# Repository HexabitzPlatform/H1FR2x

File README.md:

# H1FR2x-Hardware
Hexabitz SX1276 LoRa Module 915 MHz Module Hardware Design

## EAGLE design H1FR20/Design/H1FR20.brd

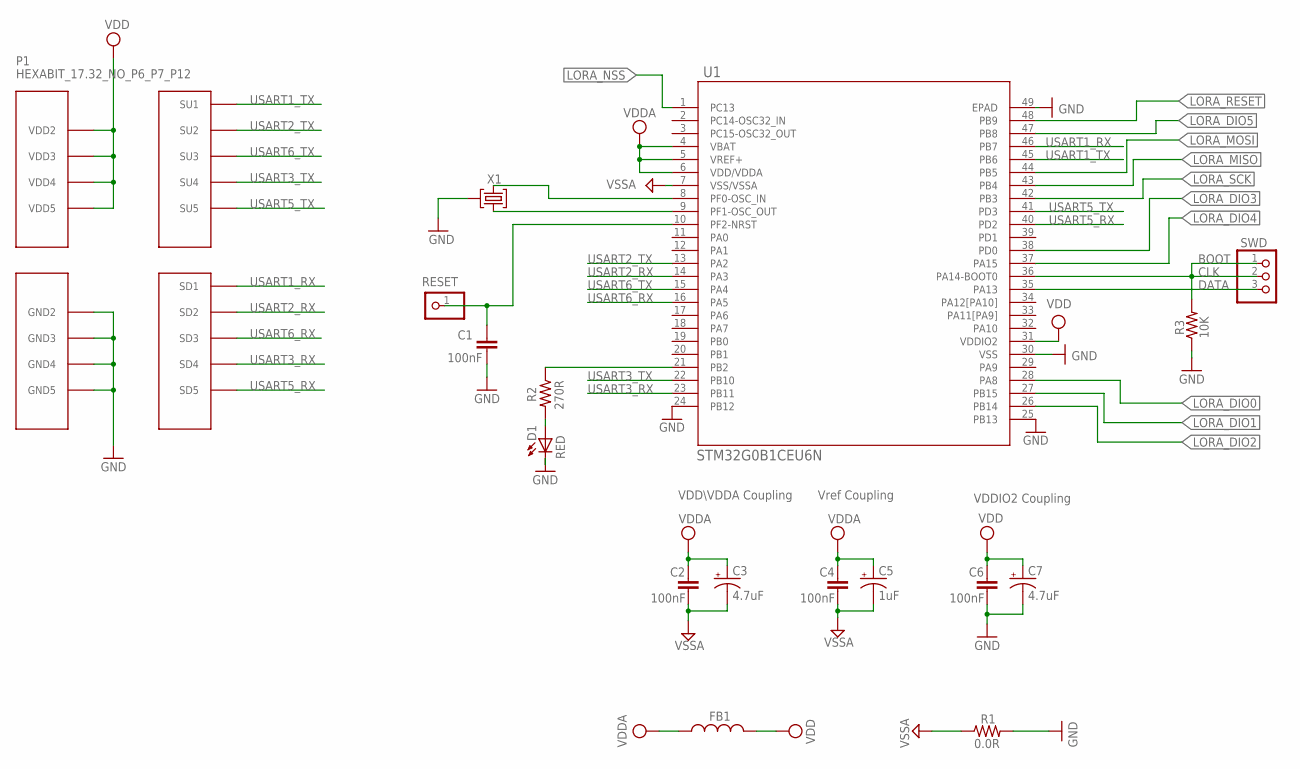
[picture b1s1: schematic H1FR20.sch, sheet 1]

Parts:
C1, C2, C4, C6: 100nF; C-0603
C3, C7: 4.7uF; C-0805-POL
C5: 1uF; C-0805-POL
D1: RED; VLMS1300-GS08; MPN VLMS1300-GS08
FB1: FB-0603
P1: HEXABIT_17.32_NO_P6_P7_P12
R1: 0.0R; R-0603
R2: 270R; R-0603
R3: 10K; R-0603
RESET: R; 1X01
SWD: PINHD-1X3SWD; SWD
U1: STM32G0B1CEU6N; HEXABITZ_ICS_QFN_B1CEU6_STM-L
X1: XTALL_CSTCE8M00G52

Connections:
CLK: R3.2, SWD.1, SWD.2, U1.36 (PA14-BOOT0)
DATA: SWD.3, U1.35 (PA13)
GND: C1.2, C6.2, C7.2 (-), D1.C, P1.PAD_PD8 (GND2), P1.PAD_PD9 (GND3), P1.PAD_PD10 (GND4), P1.PAD_PD11 (GND5), R1.2, R3.1, U1.24 (PB12), U1.25 (PB13), U1.30 (VSS), U1.49 (EPAD), X1.P$2 (2); also elsewhere on the board
LORA_DIO0: U1.28 (PA8); also elsewhere on the board
LORA_DIO1: U1.27 (PB15); also elsewhere on the board
LORA_DIO2: U1.26 (PB14); also elsewhere on the board
LORA_DIO3: U1.38 (PD0); also elsewhere on the board
LORA_DIO4: U1.37 (PA15); also elsewhere on the board
LORA_DIO5: U1.47 (PB8); also elsewhere on the board
LORA_MISO: U1.43 (PB4); also elsewhere on the board
LORA_MOSI: U1.44 (PB5); also elsewhere on the board
LORA_NSS: U1.1 (PC13); also elsewhere on the board
LORA_RESET: U1.48 (PB9); also elsewhere on the board
LORA_SCK: U1.42 (PB3); also elsewhere on the board
unnamed: D1.A, R2.2
unnamed: R2.1, U1.21 (PB2)
unnamed: U1.9 (PF1-OSC_OUT), X1.P$1 (1)
unnamed: U1.8 (PF0-OSC_IN), X1.P$3 (3)
unnamed: C1.1, RESET.1, U1.10 (PF2-NRST)
USART1_RX: P1.PAD_PD1 (SD1), U1.46 (PB7)
USART1_TX: P1.PAD_PU1 (SU1), U1.45 (PB6)
USART2_RX: P1.PAD_PD2 (SD2), U1.14 (PA3)
USART2_TX: P1.PAD_PU2 (SU2), U1.13 (PA2)
USART3_RX: P1.PAD_PD4 (SD4), U1.23 (PB11)
USART3_TX: P1.PAD_PU4 (SU4), U1.22 (PB10)
USART5_RX: P1.PAD_PD5 (SD5), U1.40 (PD2)
USART5_TX: P1.PAD_PU5 (SU5), U1.41 (PD3)
USART6_RX: P1.PAD_PD3 (SD3), U1.16 (PA5)
USART6_TX: P1.PAD_PU3 (SU3), U1.15 (PA4)
VDD: C6.1, C7.1 (+), FB1.2, P1.PAD_PU8 (VDD2), P1.PAD_PU9 (VDD3), P1.PAD_PU10 (VDD4), P1.PAD_PU11 (VDD5), U1.31 (VDDIO2); also elsewhere on the board
VDDA: C2.1, C3.1 (+), C4.1, C5.1 (+), FB1.1, U1.4 (VBAT), U1.5 (VREF+), U1.6 (VDD/VDDA)
VSSA: C2.2, C3.2 (-), C4.2, C5.2 (-), R1.1, U1.7 (VSS/VSSA)

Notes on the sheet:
Vref Coupling
VDDIO2 Coupling
VDD\VDDA Coupling
BOOT

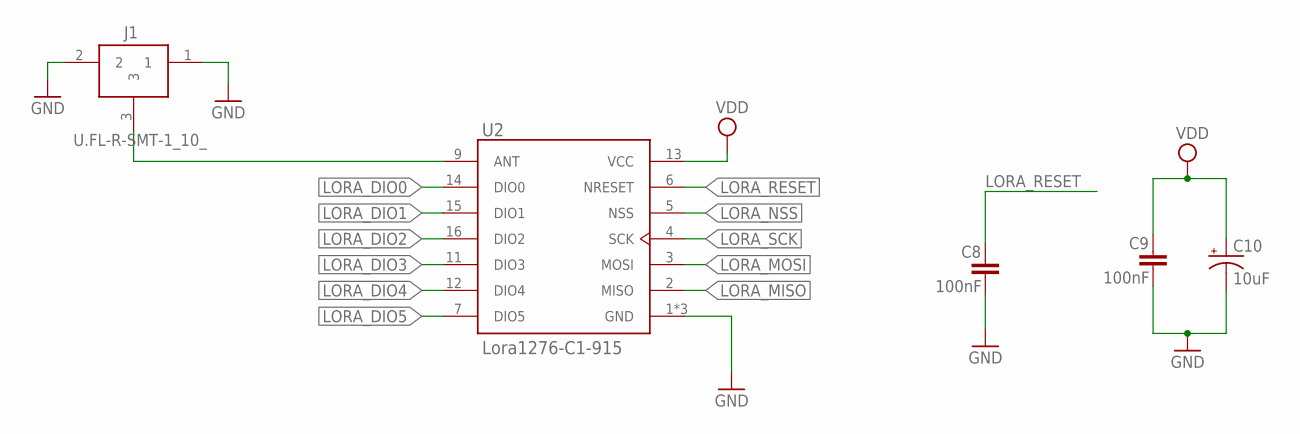
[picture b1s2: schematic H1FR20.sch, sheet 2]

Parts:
C8, C9: 100nF; C-0603
C10: 10uF; C-1210-POL
J1: U.FL-R-SMT-1_10_; U.FL-R-SMT-1(10)
U2: Lora1276-C1-915; LORA127X-C1

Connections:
GND: C8.2, C9.2, C10.2 (-), J1.1, J1.2, U2.1 (GND), U2.8 (GND), U2.10 (GND); also elsewhere on the board
LORA_DIO0: U2.14 (DIO0); also elsewhere on the board
LORA_DIO1: U2.15 (DIO1); also elsewhere on the board
LORA_DIO2: U2.16 (DIO2); also elsewhere on the board
LORA_DIO3: U2.11 (DIO3); also elsewhere on the board
LORA_DIO4: U2.12 (DIO4); also elsewhere on the board
LORA_DIO5: U2.7 (DIO5); also elsewhere on the board
LORA_MISO: U2.2 (MISO); also elsewhere on the board
LORA_MOSI: U2.3 (MOSI); also elsewhere on the board
LORA_NSS: U2.5 (NSS); also elsewhere on the board
LORA_RESET: C8.1, U2.6 (NRESET); also elsewhere on the board
LORA_SCK: U2.4 (SCK); also elsewhere on the board
unnamed: J1.3, U2.9 (ANT)
VDD: C9.1, C10.1 (+), U2.13 (VCC); also elsewhere on the board

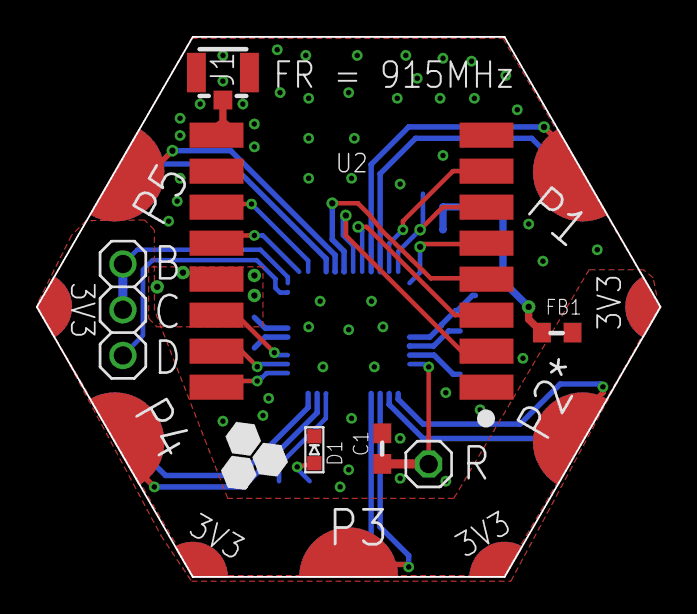
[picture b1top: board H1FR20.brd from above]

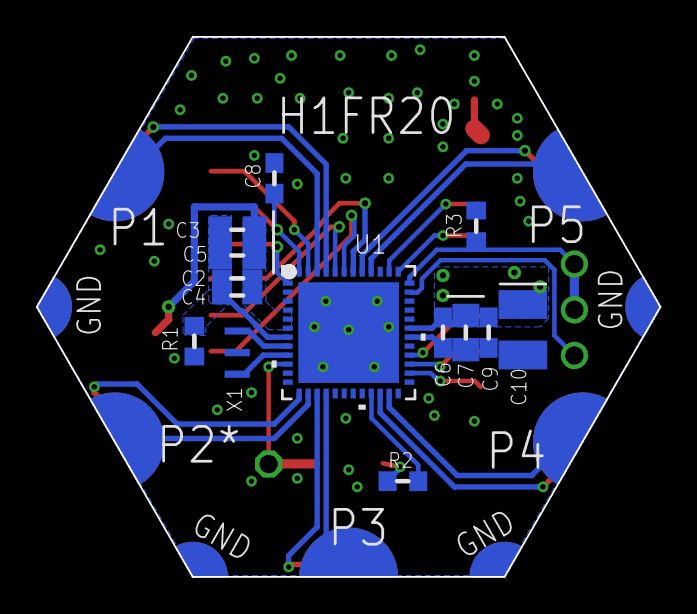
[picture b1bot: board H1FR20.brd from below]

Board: 2 copper layers, 34.6 x 30.0 mm, 22 parts (14 on the bottom side), 33 nets.

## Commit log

2023-11-15 -The first version is complete
2023-11-15 -Correct some documentation issues
2023-11-16 -Fix clearance error
2023-11-16 Fix BOM

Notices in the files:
parts and their libraries:
HEXABITZ_ICs: COPYRIGHT: Copyright (C) 2022 Ultra Librarian. All rights reserved.
